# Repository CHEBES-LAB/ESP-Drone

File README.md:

# ESP-Drone

<br>

<br>

For a full tutorial check out our [ESP32 Drone Article](https://circuitdigest.com/microcontroller-projects/DIY-wifi-controlled-drone).
For working video:  [How to build an ESP32 Drone](https://youtu.be/uzZjk0TQKtU).

Drones have rapidly evolved from niche hobbies to versatile tools with a wide range of applications, from photography to agriculture or even for defense and military purposes. Depending on the application, features and payload capacity their price will vary from pocket changes to a few million. Even though the basic principle behind these drones may appear simple, there is a lot of technology and computation that goes behind it for proper operations and a desired result from these drones. For example, maintaining stability while in the air requires precision sensors such as a Gyroscope and proper processing of reading taken with it. In this project we are going to make such a drone which can be easily controlled using our phones.
This DIY drone is small in size and can be built using easily available components such as ESP32 modules, MPU6050 IMU, coreless motors and plastic propellers.
<br>For anyone who is trying to flash the firmware using ESP32 Flash Download Tool, here are the file offsets for each binary
<br>0x1000 bootloader.bin
<br>0x10000 ESPDrone.bin
<br>0x8000 partition-table.bin
<br>
[Note: As this projects are very simple we are only providing the code, schemaitic, and a few essential images if you want to get the images or code explanations do check out the Circuit Digest website.
<br>
<br>

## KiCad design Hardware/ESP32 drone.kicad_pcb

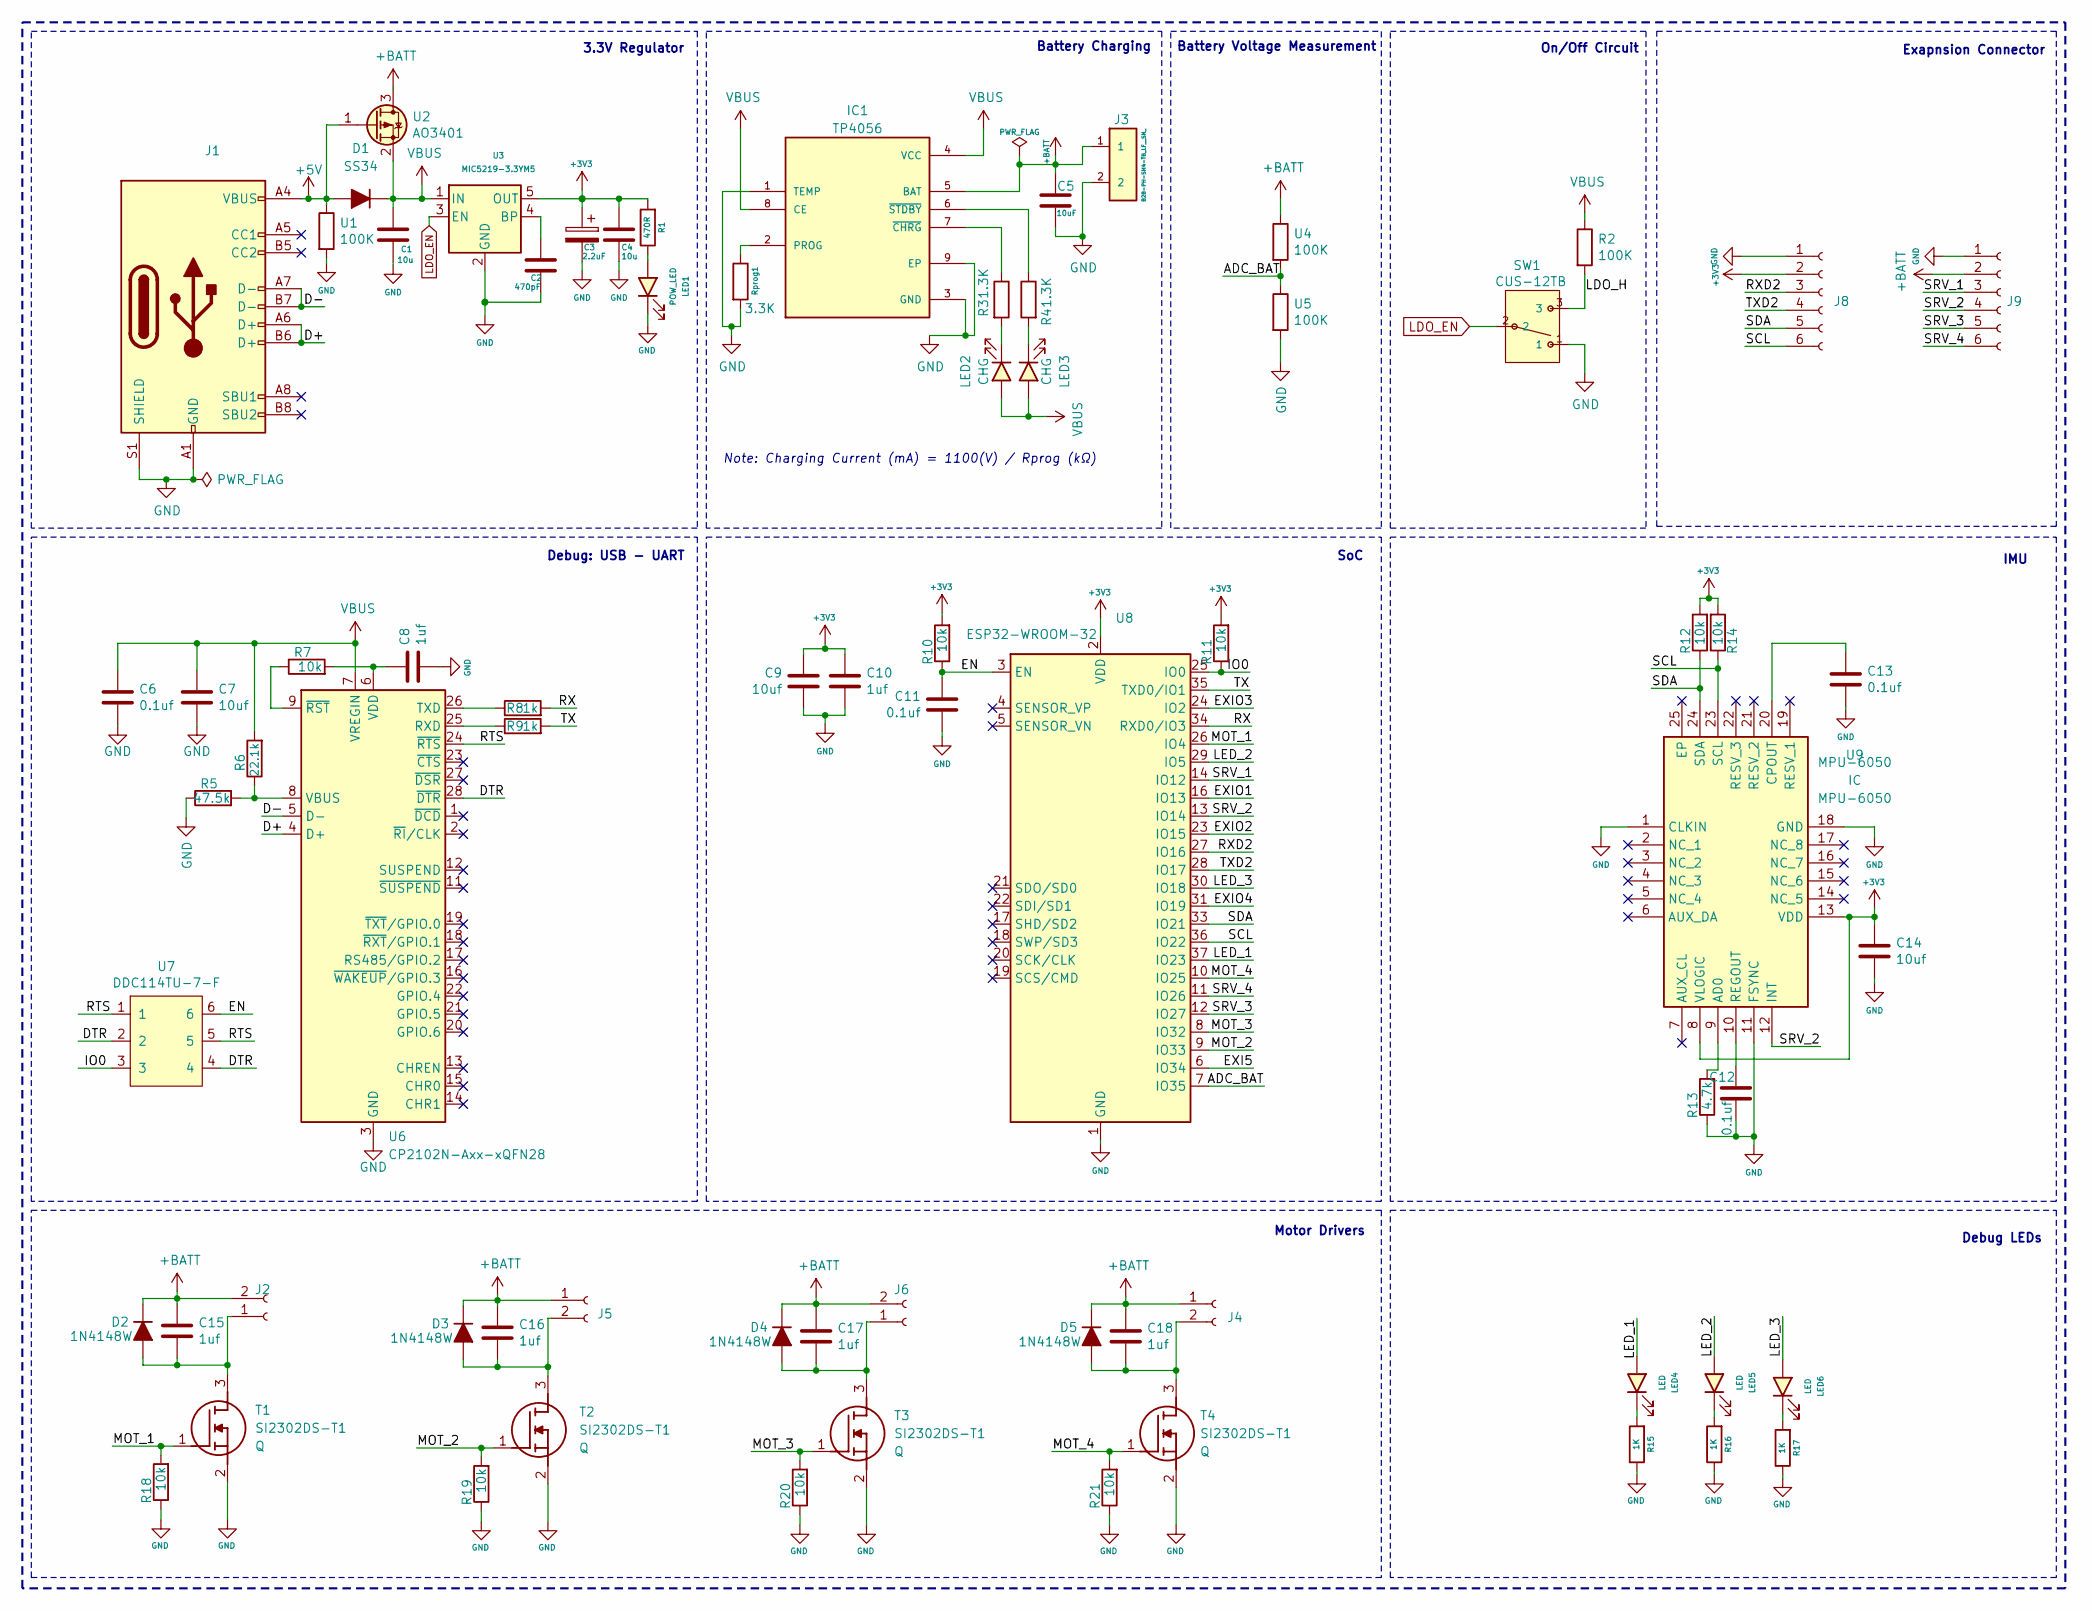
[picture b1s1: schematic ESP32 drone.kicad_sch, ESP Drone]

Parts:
C1, C4: 10u; C_0603_1608Metric
C2: 470pF; C_0603_1608Metric
C3: 2.2uF; C_0805_2012Metric
C5: 10uF; C_0603_1608Metric
C6, C11, C12, C13: 0.1uf; C_0603_1608Metric
C7, C9, C14: 10uf; C_0603_1608Metric
C8, C10, C15, C16, C17, C18: 1uf; C_0603_1608Metric
D1: SS34; D_SMA
D2, D3, D4, D5: 1N4148W; D_SOD-323
IC1: TP4056; SOP127P600X175-9N
J1: USB_C_Receptacle_USB2.0; USB_C_Receptacle_HRO_TYPE-C-31-M-12
J2, J4, J5, J6: Conn_01x02_Female; JST_GH_SM02B-GHS-TB_1x02-1MP_P1.25mm_Horizontal
J3: B2B-PH-SM4-TB_LF__SN_; SM4-CON
J8, J9: Conn_01x06_Female; PinHeader_1x06_P2.54mm_Vertical
LED1: POW_LED; LED_0603_1608Metric
LED2, LED3: CHG; LED_0603_1608Metric
LED4, LED5, LED6: LED; LED_0603_1608Metric
R1: 470R; R_0603_1608Metric
R2: 100K; R_0603_1608Metric
R3, R4: 1.3K; R_0603_1608Metric
R5: 47.5k; R_0603_1608Metric
R6: 22.1k; R_0603_1608Metric
R7, R10, R11, R12, R14, R18, R19, R20, R21: 10k; R_0603_1608Metric
R8, R9: 1k; R_0603_1608Metric
R13: 4.7k; R_0603_1608Metric
R15, R16, R17: 1K; R_0603_1608Metric
Rprog1: 3.3K; R_0603_1608Metric
SW1: CUS-12TB; CUS-12B; MANUFACTURER_PART_NUMBER CUS-12TB
T1, T2, T3, T4: SI2302DS-T1; SOT95P237X112-3N; Mouser Part Number 781-SI2302DS
U1, U4, U5: 100K; R_0603_1608Metric
U2: AO3401; SOT-23
U3: MIC5219-3.3YM5; SOT-23-5
U6: CP2102N-Axx-xQFN28; QFN-28-1EP_5x5mm_P0.5mm_EP3.35x3.35mm
U7: DDC114TU-7-F; SOT-363_SC-70-6
U8: ESP32-WROOM-32
U9: MPU-6050; QFN50P400X400X95-24N; Mouser Part Number 410-MPU-6050

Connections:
+3V3: C3.1, C4.1, C9.1, C10.1, C14.1, J8.2, R1.2, R10.2, R11.2, R12.2, R14.2, U3.5 (OUT), U8.2 (VDD), U9.8 (VLOGIC), U9.13 (VDD)
+5V: D1.2 (A), J1.A4 (VBUS), J1.A9 (VBUS), J1.B4 (VBUS), J1.B9 (VBUS), U1.1, U2.1 (G)
+BATT: C5.1, C15.1, C16.1, C17.1, C18.1, D2.1 (K), D3.1 (K), D4.1 (K), D5.1 (K), IC1.5 (BAT), J2.2, J3.1, J4.1, J5.1, J6.2, J9.2, U2.3 (D), U4.1
/ADC_BAT: U4.2, U5.1, U8.7 (IO35)
/D+: J1.A6 (D+), J1.B6 (D+), U6.4 (D+)
/D-: J1.A7 (D-), J1.B7 (D-), U6.5 (D-)
/DTR: U6.28 (~DTR), U7.2, U7.4
/EN: C11.1, R10.1, U7.6, U8.3 (EN)
/EXI5: U8.6 (IO34)
/EXIO1: U8.16 (IO13)
/EXIO2: U8.23 (IO15)
/EXIO3: U8.24 (IO2)
/EXIO4: U8.31 (IO19)
/IO0: R11.1, U7.3, U8.25 (IO0)
/LDO_H: R2.2, SW1.3 (C)
/LED_1: LED4.2 (A), U8.37 (IO23)
/LED_2: LED5.2 (A), U8.29 (IO5)
/LED_3: LED6.2 (A), U8.30 (IO18)
/MOT_1: R18.2, T1.1 (G), U8.26 (IO4)
/MOT_2: R19.2, T2.1 (G), U8.9 (IO33)
/MOT_3: R20.2, T3.1 (G), U8.8 (IO32)
/MOT_4: R21.2, T4.1 (G), U8.10 (IO25)
/RTS: U6.24 (~RTS), U7.1, U7.5
/RX: R8.2, U8.34 (RXD0/IO3)
/RXD2: J8.3, U8.27 (IO16)
/SCL: J8.6, R14.1, U8.36 (IO22), U9.23 (SCL)
/SDA: J8.5, R12.1, U8.33 (IO21), U9.24 (SDA)
/SRV_1: J9.3, U8.14 (IO12)
/SRV_2: J9.4, U8.13 (IO14), U9.12 (INT)
/SRV_3: J9.5, U8.12 (IO27)
/SRV_4: J9.6, U8.11 (IO26)
/TX: R9.2, U8.35 (TXD0/IO1)
/TXD2: J8.4, U8.28 (IO17)
GND: C1.2, C2.2, C3.2, C4.2, C5.2, C6.2, C7.2, C8.2, C9.2, C10.2, C11.2, C12.2, C13.2, C14.2, IC1.1 (TEMP), IC1.3 (GND), IC1.9 (EP), J1.A1 (GND), J1.A12 (GND), J1.B1 (GND), J1.B12 (GND), J1.S1 (SHIELD), J3.2, J8.1, J9.1, LED1.1 (K), R5.1, R13.1, R15.1, R16.1, R17.1, R18.1, R19.1, R20.1, R21.1, Rprog1.2, SW1.1 (A), SW1.4, T1.2 (S), T2.2 (S), T3.2 (S), T4.2 (S), U1.2, U3.2 (GND), U5.2, U6.3 (GND), U6.29 (GND), U8.1 (GND), U8.15 (GND), U8.38 (GND), U8.39 (GND), U9.1 (CLKIN), U9.11 (FSYNC), U9.18 (GND)
LDO_EN: SW1.2 (B), U3.3 (EN)
unnamed: C15.2, D2.2 (A), J2.1, T1.3 (D)
unnamed: C16.2, D3.2 (A), J5.2, T2.3 (D)
unnamed: C17.2, D4.2 (A), J6.1, T3.3 (D)
unnamed: C18.2, D5.2 (A), J4.2, T4.3 (D)
unnamed: IC1.2 (PROG), Rprog1.1
unnamed: IC1.7 (~CHRG), R3.1
unnamed: IC1.6 (~STDBY), R4.1
unnamed: LED1.2 (A), R1.1
unnamed: LED2.1 (K), R3.2
unnamed: LED3.1 (K), R4.2
unnamed: LED4.1 (K), R15.2
unnamed: LED5.1 (K), R16.2
unnamed: LED6.1 (K), R17.2
unnamed: C2.1, U3.4 (BP)
unnamed: R9.1, U6.25 (RXD)
unnamed: R8.1, U6.26 (TXD)
unnamed: R5.2, R6.1, U6.8 (VBUS)
unnamed: C8.1, R7.2, U6.6 (VDD)
unnamed: R7.1, U6.9 (~RST)
unnamed: R13.2, U9.9 (AD0)
unnamed: C13.1, U9.20 (CPOUT)
unnamed: C12.1, U9.10 (REGOUT)
VBUS: C1.1, C6.1, C7.1, D1.1 (K), IC1.4 (VCC), IC1.8 (CE), LED2.2 (A), LED3.2 (A), R2.1, R6.2, U2.2 (S), U3.1 (IN), U6.7 (VREGIN)

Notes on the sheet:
SoC
Battery Voltage Measurement
IMU
Motor Drivers
Battery Charging
Debug LEDs
Debug: USB - UART
Exapnsion Connector
3.3V Regulator
Note: Charging Current (mA) = 1100(V) / Rprog (kΩ)
On/Off Circuit

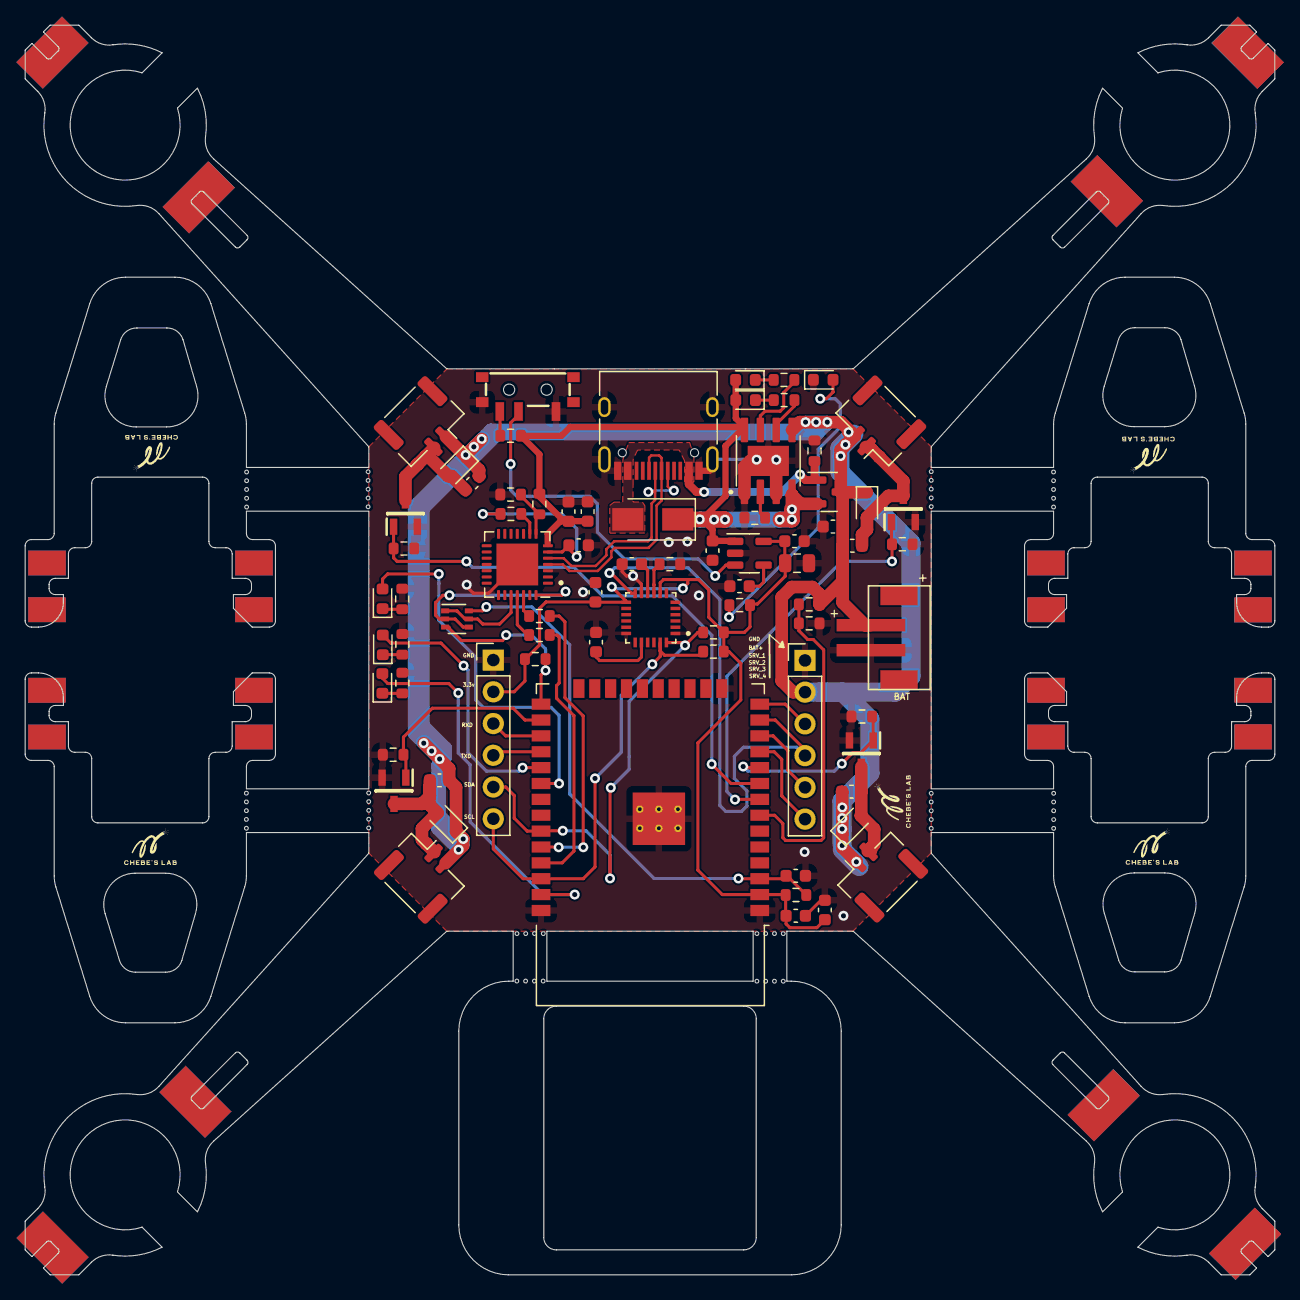
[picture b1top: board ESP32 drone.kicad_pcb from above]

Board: 2 copper layers, 100.0 x 100.0 mm, 74 parts (0 on the bottom side), 53 nets.

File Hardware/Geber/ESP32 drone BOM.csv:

"Reference","Value","Datasheet","Footprint","Qty","DNP"
"C1,C4","10u","~","Capacitor_SMD:C_0603_1608Metric","2",""
"C2","470pF","~","Capacitor_SMD:C_0603_1608Metric","1",""
"C3","2.2uF","~","Capacitor_SMD:C_0805_2012Metric","1",""
"C5","10uF","~","Capacitor_SMD:C_0603_1608Metric","1",""
"C6,C11,C12,C13","0.1uf","~","Capacitor_SMD:C_0603_1608Metric","4",""
"C7,C9,C14","10uf","~","Capacitor_SMD:C_0603_1608Metric","3",""
"C8,C10,C15,C16,C17,C18","1uf","~","Capacitor_SMD:C_0603_1608Metric","6",""
"D1","SS34","https://www.diodes.com/assets/Datasheets/ds16008.pdf","Diode_SMD:D_SMA","1",""
"D2,D3,D4,D5","1N4148W","https://www.vishay.com/docs/85748/1n4148w.pdf","Diode_SMD:D_SOD-323","4",""
"IC1","TP4056","","AddedLibraries:SOP127P600X175-9N","1",""
"J1","USB_C_Receptacle_USB2.0","https://www.usb.org/sites/default/files/documents/usb_type-c.zip","Connector_USB:USB_C_Receptacle_HRO_TYPE-C-31-M-12","1",""
"J2,J4,J5,J6","Conn_01x02_Female","~","Connector_JST:JST_GH_SM02B-GHS-TB_1x02-1MP_P1.25mm_Horizontal","4",""
"J3","B2B-PH-SM4-TB_LF__SN_","","AddedLibraries:SM4-CON","1",""
"J8,J9","Conn_01x06_Female","~","Connector_PinHeader_2.54mm:PinHeader_1x06_P2.54mm_Vertical","2",""
"LED1","POW_LED","~","LED_SMD:LED_0603_1608Metric","1",""
"LED2,LED3","CHG","~","LED_SMD:LED_0603_1608Metric","2",""
"LED4,LED5,LED6","LED","~","LED_SMD:LED_0603_1608Metric","3",""
"R1","470R","~","Resistor_SMD:R_0603_1608Metric","1",""
"R2,U1,U4,U5","100K","~","Resistor_SMD:R_0603_1608Metric","4",""
"R3,R4","1.3K","~","Resistor_SMD:R_0603_1608Metric","2",""
"R5","47.5k","~","Resistor_SMD:R_0603_1608Metric","1",""
"R6","22.1k","~","Resistor_SMD:R_0603_1608Metric","1",""
"R7,R10,R11,R12,R14,R18,R19,R20,R21","10k","~","Resistor_SMD:R_0603_1608Metric","9",""
"R8,R9","1k","~","Resistor_SMD:R_0603_1608Metric","2",""
"R13","4.7k","~","Resistor_SMD:R_0603_1608Metric","1",""
"R15,R16,R17","1K","~","Resistor_SMD:R_0603_1608Metric","3",""
"Rprog1","3.3K","~","Resistor_SMD:R_0603_1608Metric","1",""
"SW1","CUS-12TB","","AddedLibraries:CUS-12B","1",""
"T1,T2,T3,T4","SI2302DS-T1","https://4donline.ihs.com/images/VipMasterIC/IC/SILX/SILXS081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","AddedLibraries:SOT95P237X112-3N","4",""
"U2","AO3401","~","Package_TO_SOT_SMD:SOT-23","1",""
"U3","MIC5219-3.3YM5","http://ww1.microchip.com/downloads/en/DeviceDoc/MIC5219-500m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","Package_TO_SOT_SMD:SOT-23-5","1",""
"U6","CP2102N-Axx-xQFN28","https://www.silabs.com/documents/public/data-sheets/cp2102n-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","Package_DFN_QFN:QFN-28-1EP_5x5mm_P0.5mm_EP3.35x3.35mm","1",""
"U7","DDC114TU-7-F","","Package_TO_SOT_SMD:SOT-363_SC-70-6","1",""
"U8","ESP32-WROOM-32","https://www.espressif.com/sites/default/files/documentation/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","RF_Module:ESP32-WROOM-32","1",""
"U9","MPU-6050","","AddedLibraries:QFN50P400X400X95-24N","1",""

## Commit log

2024-07-10 final hardware
